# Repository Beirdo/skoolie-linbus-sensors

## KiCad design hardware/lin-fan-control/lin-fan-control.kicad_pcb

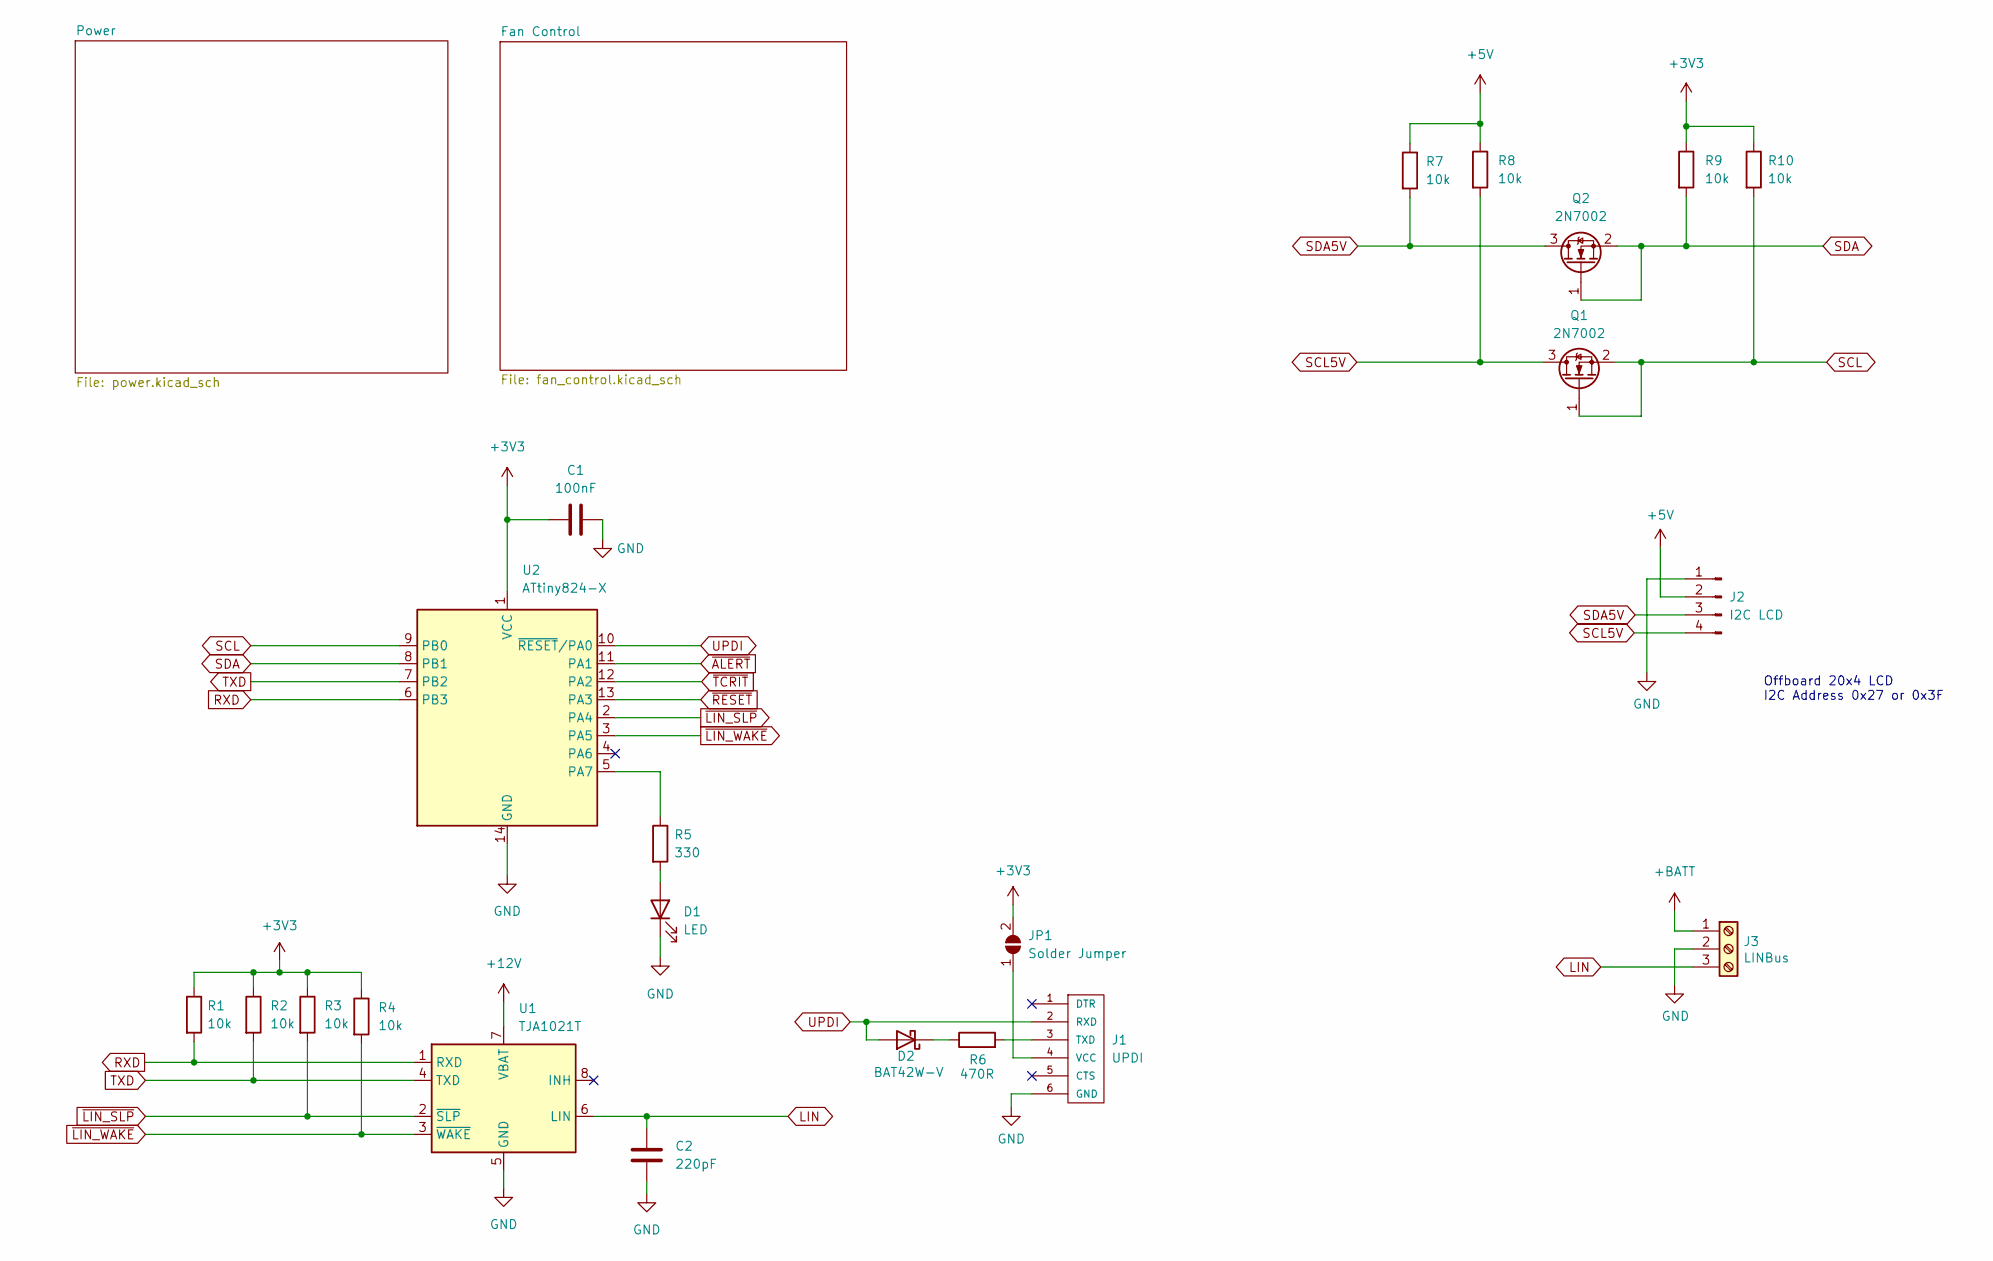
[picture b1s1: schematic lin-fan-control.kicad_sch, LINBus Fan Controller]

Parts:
C1: 100nF; C_0805_2012Metric_Pad1.18x1.45mm_HandSolder
C2: 220pF; C_0805_2012Metric_Pad1.18x1.45mm_HandSolder
D1: LED; LED_0805_2012Metric_Pad1.15x1.40mm_HandSolder
D2: BAT42W-V; D_SOD-123
J1: UPDI; FTDI-TARGET
J2: I2C LCD; PinHeader_1x04_P2.54mm_Vertical
J3: LINBus; TerminalBlock_TE_282834-3_1x03_P2.54mm_Horizontal
JP1: Solder Jumper; SolderJumper-2_P1.3mm_Open_TrianglePad1.0x1.5mm
Q1, Q2: 2N7002; SOT-23
R1, R2, R3, R4, R7, R8, R9, R10: 10k; R_0805_2012Metric_Pad1.20x1.40mm_HandSolder
R5: 330; R_0805_2012Metric_Pad1.20x1.40mm_HandSolder
R6: 470R; R_0805_2012Metric_Pad1.20x1.40mm_HandSolder
U1: TJA1021T; SOIC-8_3.9x4.9mm_P1.27mm
U2: ATtiny824-X; TSSOP-14_4.4x5mm_P0.65mm

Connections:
+3V3: C1.2, JP1.2 (B), R1.1, R2.1, R3.1, R4.1, R9.1, R10.1, U2.1 (VCC); also elsewhere on the board
+5V: J2.2, R7.1, R8.1; also elsewhere on the board
+12V: U1.7 (VBAT); also elsewhere on the board
+BATT: J3.1; also elsewhere on the board
GND: C1.1, C2.2, D1.1 (K), J1.6 (GND), J2.1, J3.2, U1.5 (GND), U2.14 (GND); also elsewhere on the board
LIN: C2.1, J3.3, U1.6 (LIN)
unnamed: D1.2 (A), R5.2
unnamed: D2.1 (K), R6.1
unnamed: J1.4 (VCC), JP1.1 (A)
unnamed: R5.1, U2.5 (PA7)
unnamed: J1.3 (TXD), R6.2
RXD: R1.2, U1.1 (RXD), U2.6 (PB3)
SCL: Q1.1 (G), Q1.2 (S), R10.2, U2.9 (PB0); also elsewhere on the board
SCL5V: J2.4, Q1.3 (D), R8.2
SDA: Q2.1 (G), Q2.2 (S), R9.2, U2.8 (PB1); also elsewhere on the board
SDA5V: J2.3, Q2.3 (D), R7.2
TXD: R2.2, U1.4 (TXD), U2.7 (PB2)
UPDI: D2.2 (A), J1.2 (RXD), U2.10 (~RESET/PA0)
~ALERT: U2.11 (PA1); also elsewhere on the board
~LIN_SLP: R3.2, U1.2 (~SLP), U2.2 (PA4)
~LIN_WAKE: R4.2, U1.3 (~WAKE), U2.3 (PA5)
~RESET: U2.13 (PA3)
~TCRIT: U2.12 (PA2); also elsewhere on the board

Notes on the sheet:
Offboard 20x4 LCD I2C Address 0x27 or 0x3F

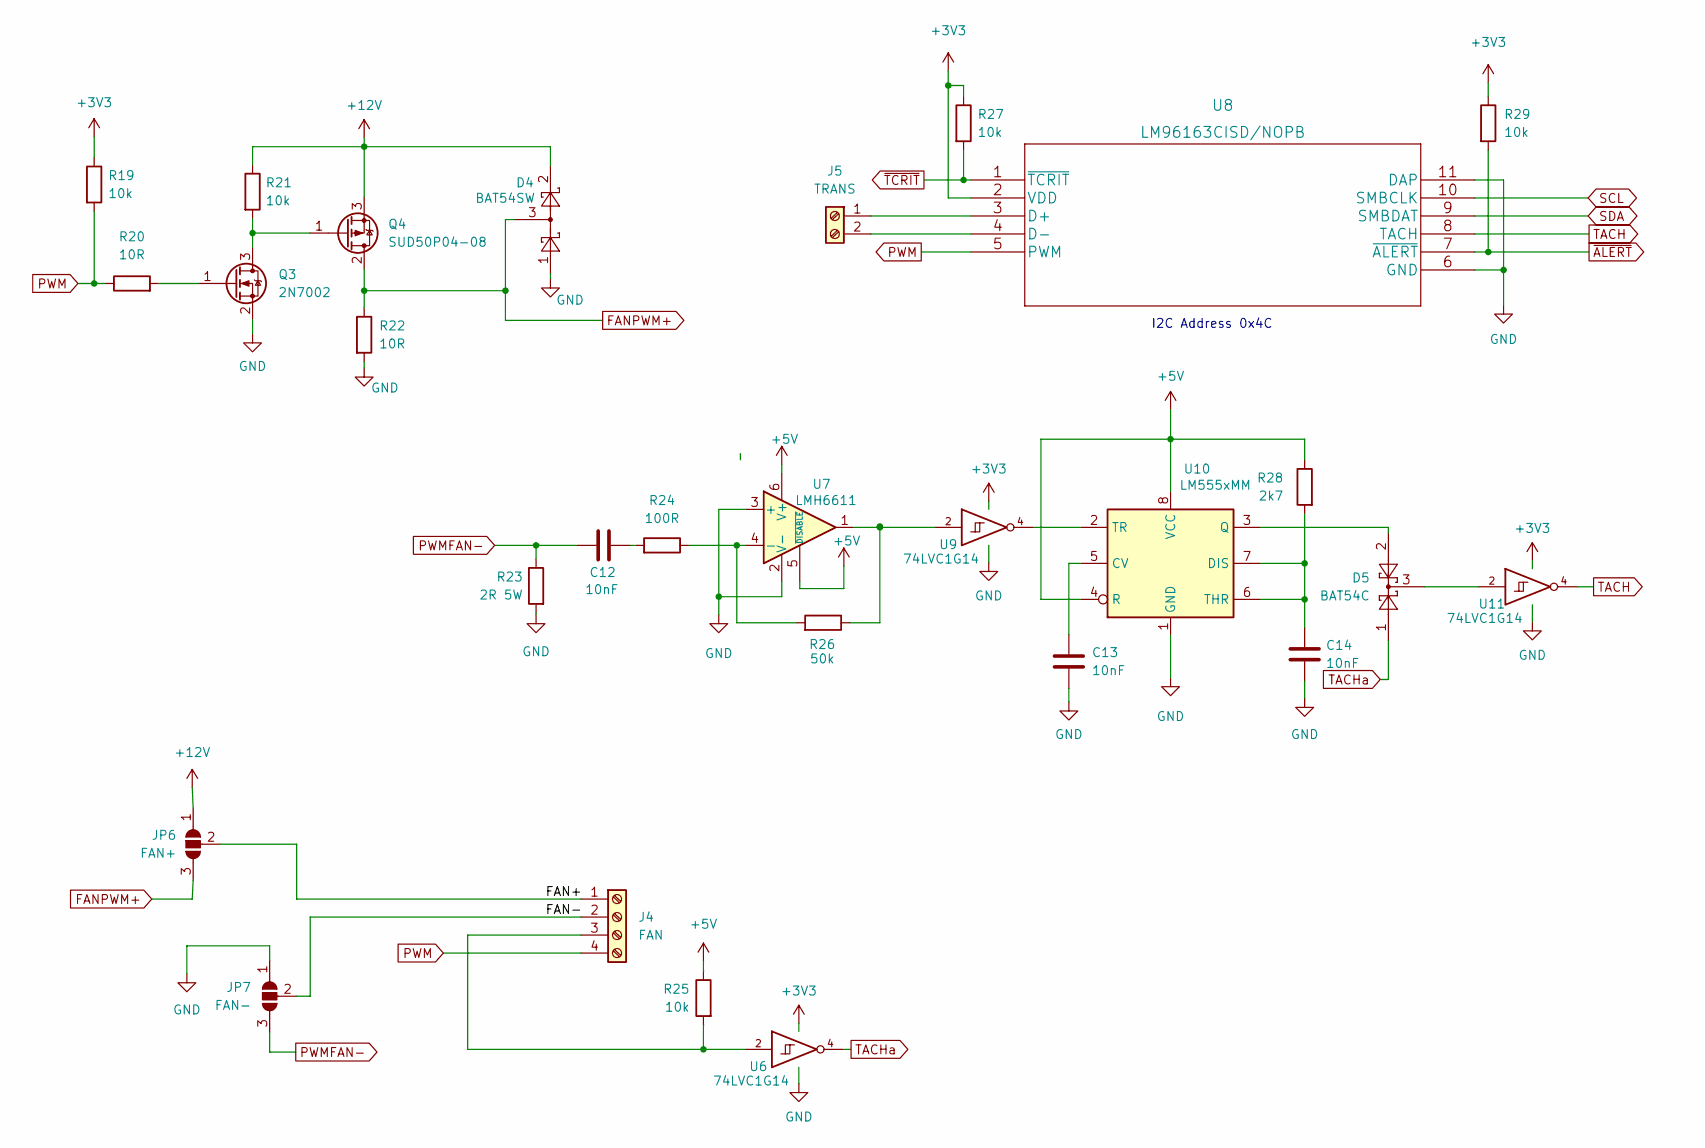
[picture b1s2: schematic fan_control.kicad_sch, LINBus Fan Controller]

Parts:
C12, C13, C14: 10nF; C_0805_2012Metric_Pad1.18x1.45mm_HandSolder
D4: BAT54SW; SOT-323_SC-70
D5: BAT54C; SOT-23
J4: FAN; TerminalBlock_TE_282834-4_1x04_P2.54mm_Horizontal
J5: TRANS; TerminalBlock_TE_282834-2_1x02_P2.54mm_Horizontal
JP6: FAN+; SolderJumper-3_P2.0mm_Open_TrianglePad1.0x1.5mm
JP7: FAN-; SolderJumper-3_P2.0mm_Open_TrianglePad1.0x1.5mm
Q3: 2N7002; SOT-23
Q4: SUD50P04-08; TO-252-2
R19, R21, R25, R27, R29: 10k; R_0805_2012Metric_Pad1.20x1.40mm_HandSolder
R20, R22: 10R; R_0805_2012Metric_Pad1.20x1.40mm_HandSolder
R23: 2R 5W; 355010RFT
R24: 100R; R_0805_2012Metric_Pad1.20x1.40mm_HandSolder
R26: 50k; R_0805_2012Metric_Pad1.20x1.40mm_HandSolder
R28: 2k7; R_0805_2012Metric_Pad1.20x1.40mm_HandSolder
U6, U9, U11: 74LVC1G14; SOT-353_SC-70-5_Handsoldering
U7: LMH6611; TSOT-23-6
U8: LM96163CISD/NOPB; LM96163CISD&slash_NOPB
U10: LM555xMM; VSSOP-8_3.0x3.0mm_P0.65mm

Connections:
+3V3: R19.1, R27.1, R29.1, U6.5 (VCC), U8.2 (VDD), U9.5 (VCC), U11.5 (VCC); also elsewhere on the board
+5V: R25.1, R28.1, U7.5 (~DISABLE), U7.6 (V+), U10.4 (R), U10.8 (VCC); also elsewhere on the board
+12V: D4.2, JP6.1 (A), Q4.3 (S), R21.1; also elsewhere on the board
/Fan Control/FAN+: J4.1, JP6.2 (C)
/Fan Control/FAN-: J4.2, JP7.2 (C)
FANPWM+: D4.3, JP6.3 (B), Q4.2 (D), R22.1
GND: C13.2, C14.2, D4.1, JP7.1 (A), Q3.2 (S), R22.2, R23.2, U6.3 (GND), U7.2 (V-), U7.3 (+), U8.6 (GND), U8.11 (DAP), U9.3 (GND), U10.1 (GND), U11.3 (GND); also elsewhere on the board
unnamed: C12.1, R24.2
unnamed: C13.1, U10.5 (CV)
unnamed: C14.1, R28.2, U10.6 (THR), U10.7 (DIS)
unnamed: D5.2, U10.3 (Q)
unnamed: D5.3, U11.2
unnamed: J4.3, R25.2, U6.2
unnamed: J5.1, U8.3 (D+)
unnamed: J5.2, U8.4 (D-)
unnamed: Q3.1 (G), R20.2
unnamed: Q3.3 (D), Q4.1 (G), R21.2
unnamed: R24.1, R26.2, U7.4 (-)
unnamed: R26.1, U7.1, U9.2
unnamed: U9.4, U10.2 (TR)
PWM: J4.4, R19.2, R20.1, U8.5 (PWM)
PWMFAN-: C12.2, JP7.3 (B), R23.1
SCL: U8.10 (SMBCLK); also elsewhere on the board
SDA: U8.9 (SMBDAT); also elsewhere on the board
TACH: U8.8 (TACH), U11.4
TACHa: D5.1, U6.4
~ALERT: R29.2, U8.7 (~ALERT); also elsewhere on the board
~TCRIT: R27.2, U8.1 (~TCRIT); also elsewhere on the board

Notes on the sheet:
I2C Address 0x4C

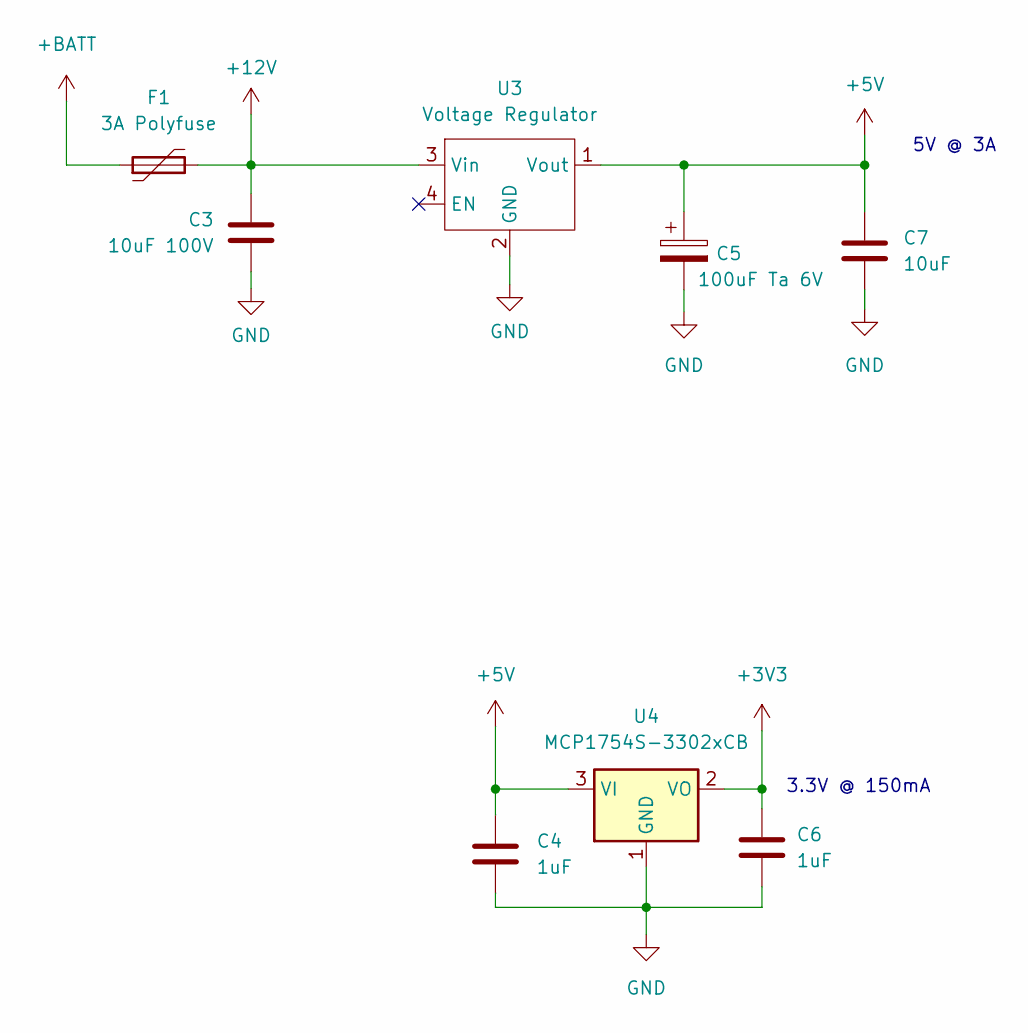
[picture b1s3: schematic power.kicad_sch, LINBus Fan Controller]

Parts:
C3: 10uF 100V; C_1210_3225Metric_Pad1.33x2.70mm_HandSolder
C4, C6: 1uF; C_0805_2012Metric_Pad1.18x1.45mm_HandSolder
C5: 100uF Ta 6V; CP_EIA-3216-10_Kemet-I_Pad1.58x1.35mm_HandSolder
C7: 10uF; C_0805_2012Metric_Pad1.18x1.45mm_HandSolder
F1: 3A Polyfuse; R_1812_4532Metric_Pad1.30x3.40mm_HandSolder; Digikey F2772CT-ND
U3: Voltage Regulator; Switching_Regulator_Module
U4: MCP1754S-3302xCB; SOT-23

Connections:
+3V3: C6.1, U4.2 (VO); also elsewhere on the board
+5V: C4.1, C5.1, C7.1, U3.1 (Vout), U4.3 (VI); also elsewhere on the board
+12V: C3.1, F1.2, U3.3 (Vin); also elsewhere on the board
+BATT: F1.1; also elsewhere on the board
GND: C3.2, C4.2, C5.2, C6.2, C7.2, U3.2 (GND), U4.1 (GND); also elsewhere on the board

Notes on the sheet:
5V @ 3A
3.3V @ 150mA

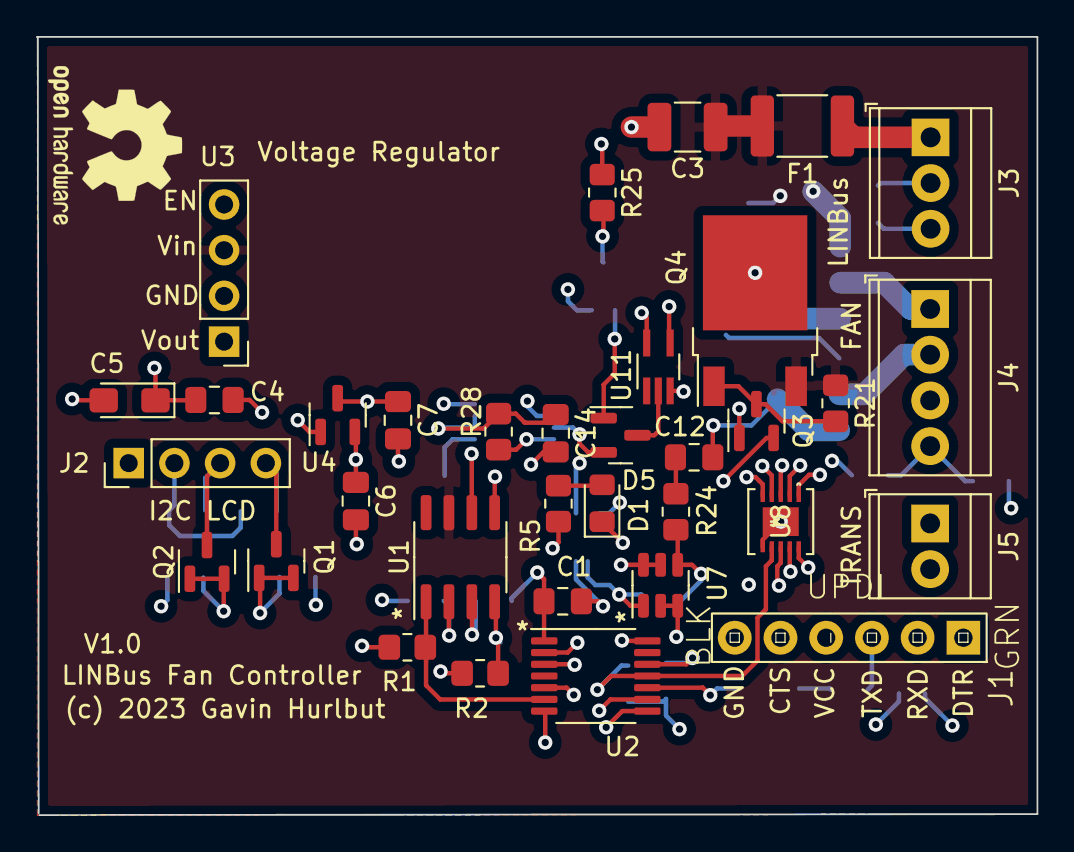
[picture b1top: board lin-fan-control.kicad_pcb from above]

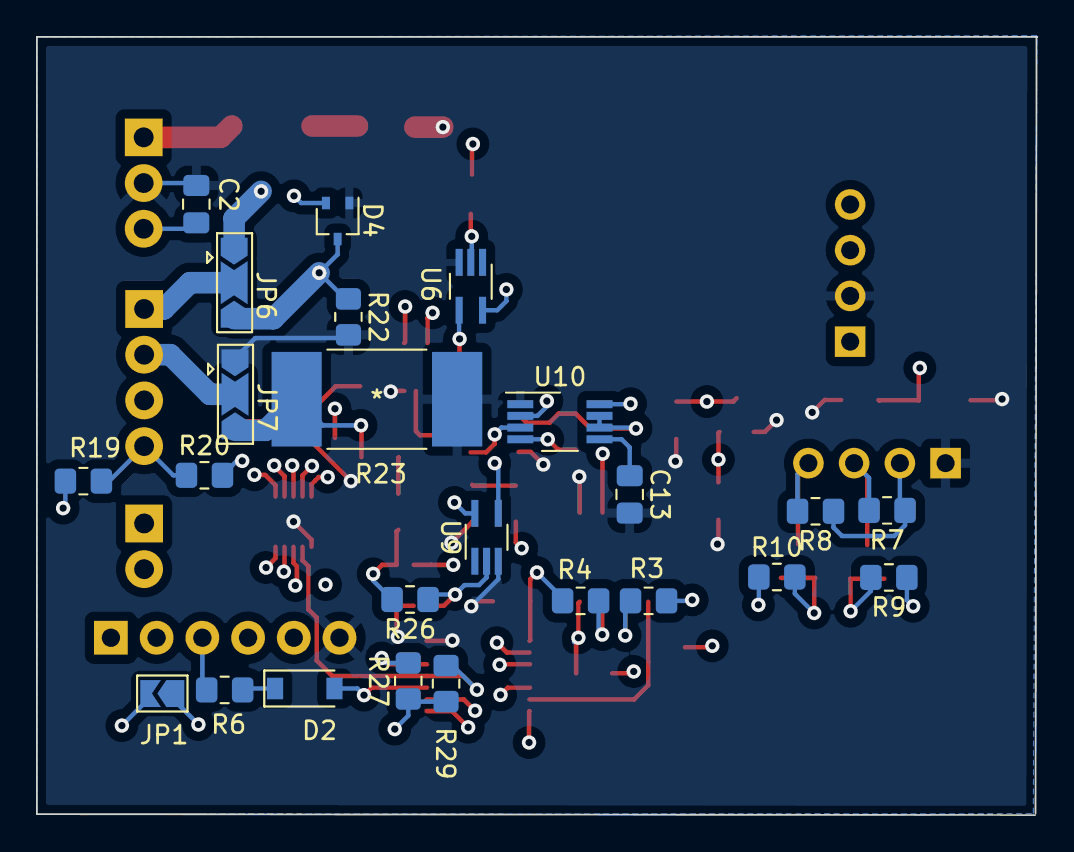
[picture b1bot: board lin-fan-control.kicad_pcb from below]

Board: 4 copper layers, 55.6 x 43.2 mm, 58 parts (24 on the bottom side), 42 nets.

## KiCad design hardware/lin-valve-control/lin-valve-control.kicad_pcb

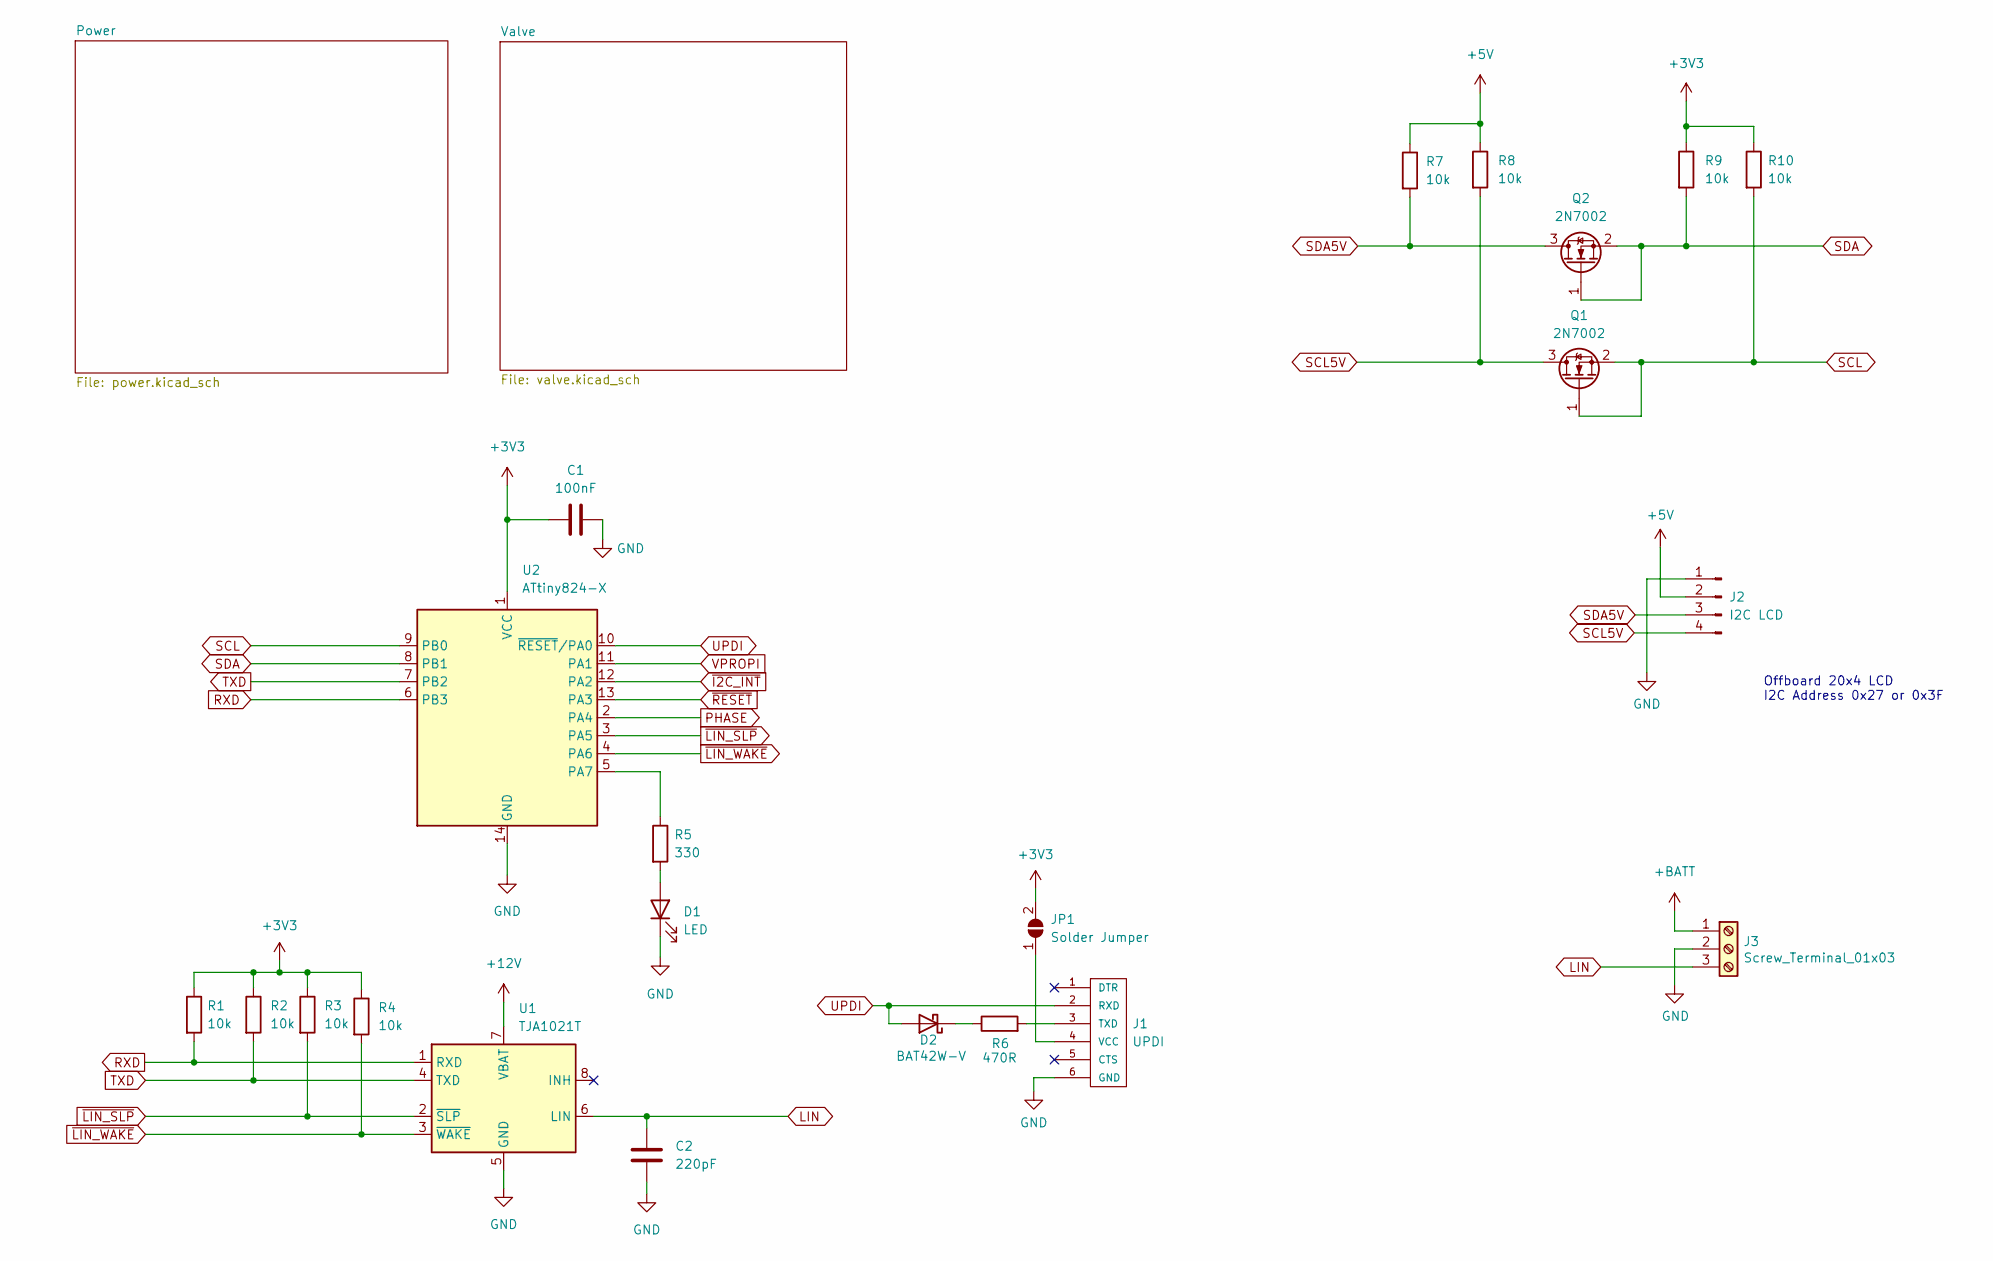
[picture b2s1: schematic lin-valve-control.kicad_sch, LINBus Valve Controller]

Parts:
C1: 100nF; C_0805_2012Metric_Pad1.18x1.45mm_HandSolder
C2: 220pF; C_0805_2012Metric_Pad1.18x1.45mm_HandSolder
D1: LED; LED_0805_2012Metric_Pad1.15x1.40mm_HandSolder
D2: BAT42W-V; D_SOD-123
J1: UPDI; FTDI-TARGET
J2: I2C LCD; PinHeader_1x04_P2.54mm_Vertical
J3: Screw_Terminal_01x03; TerminalBlock_TE_282834-3_1x03_P2.54mm_Horizontal
JP1: Solder Jumper; SolderJumper-2_P1.3mm_Open_TrianglePad1.0x1.5mm
Q1, Q2: 2N7002; SOT-23
R1, R2, R3, R4, R7, R8, R9, R10: 10k; R_0805_2012Metric_Pad1.20x1.40mm_HandSolder
R5: 330; R_0805_2012Metric_Pad1.20x1.40mm_HandSolder
R6: 470R; R_0805_2012Metric_Pad1.20x1.40mm_HandSolder
U1: TJA1021T; SOIC-8_3.9x4.9mm_P1.27mm
U2: ATtiny824-X; TSSOP-14_4.4x5mm_P0.65mm

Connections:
+3V3: C1.2, JP1.2 (B), R1.1, R2.1, R3.1, R4.1, R9.1, R10.1, U2.1 (VCC); also elsewhere on the board
+5V: J2.2, R7.1, R8.1; also elsewhere on the board
+12V: U1.7 (VBAT); also elsewhere on the board
+BATT: J3.1; also elsewhere on the board
GND: C1.1, C2.2, D1.1 (K), J1.6 (GND), J2.1, J3.2, U1.5 (GND), U2.14 (GND); also elsewhere on the board
LIN: C2.1, J3.3, U1.6 (LIN)
unnamed: D1.2 (A), R5.2
unnamed: D2.1 (K), R6.1
unnamed: J1.3 (TXD), R6.2
unnamed: J1.4 (VCC), JP1.1 (A)
unnamed: R5.1, U2.5 (PA7)
PHASE: U2.2 (PA4); also elsewhere on the board
RXD: R1.2, U1.1 (RXD), U2.6 (PB3)
SCL: Q1.1 (G), Q1.2 (S), R10.2, U2.9 (PB0); also elsewhere on the board
SCL5V: J2.4, Q1.3 (D), R8.2
SDA: Q2.1 (G), Q2.2 (S), R9.2, U2.8 (PB1); also elsewhere on the board
SDA5V: J2.3, Q2.3 (D), R7.2
TXD: R2.2, U1.4 (TXD), U2.7 (PB2)
UPDI: D2.2 (A), J1.2 (RXD), U2.10 (~RESET/PA0)
VPROPI: U2.11 (PA1); also elsewhere on the board
~I2C_INT: U2.12 (PA2); also elsewhere on the board
~LIN_SLP: R3.2, U1.2 (~SLP), U2.3 (PA5)
~LIN_WAKE: R4.2, U1.3 (~WAKE), U2.4 (PA6)
~RESET: U2.13 (PA3)

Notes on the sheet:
Offboard 20x4 LCD I2C Address 0x27 or 0x3F

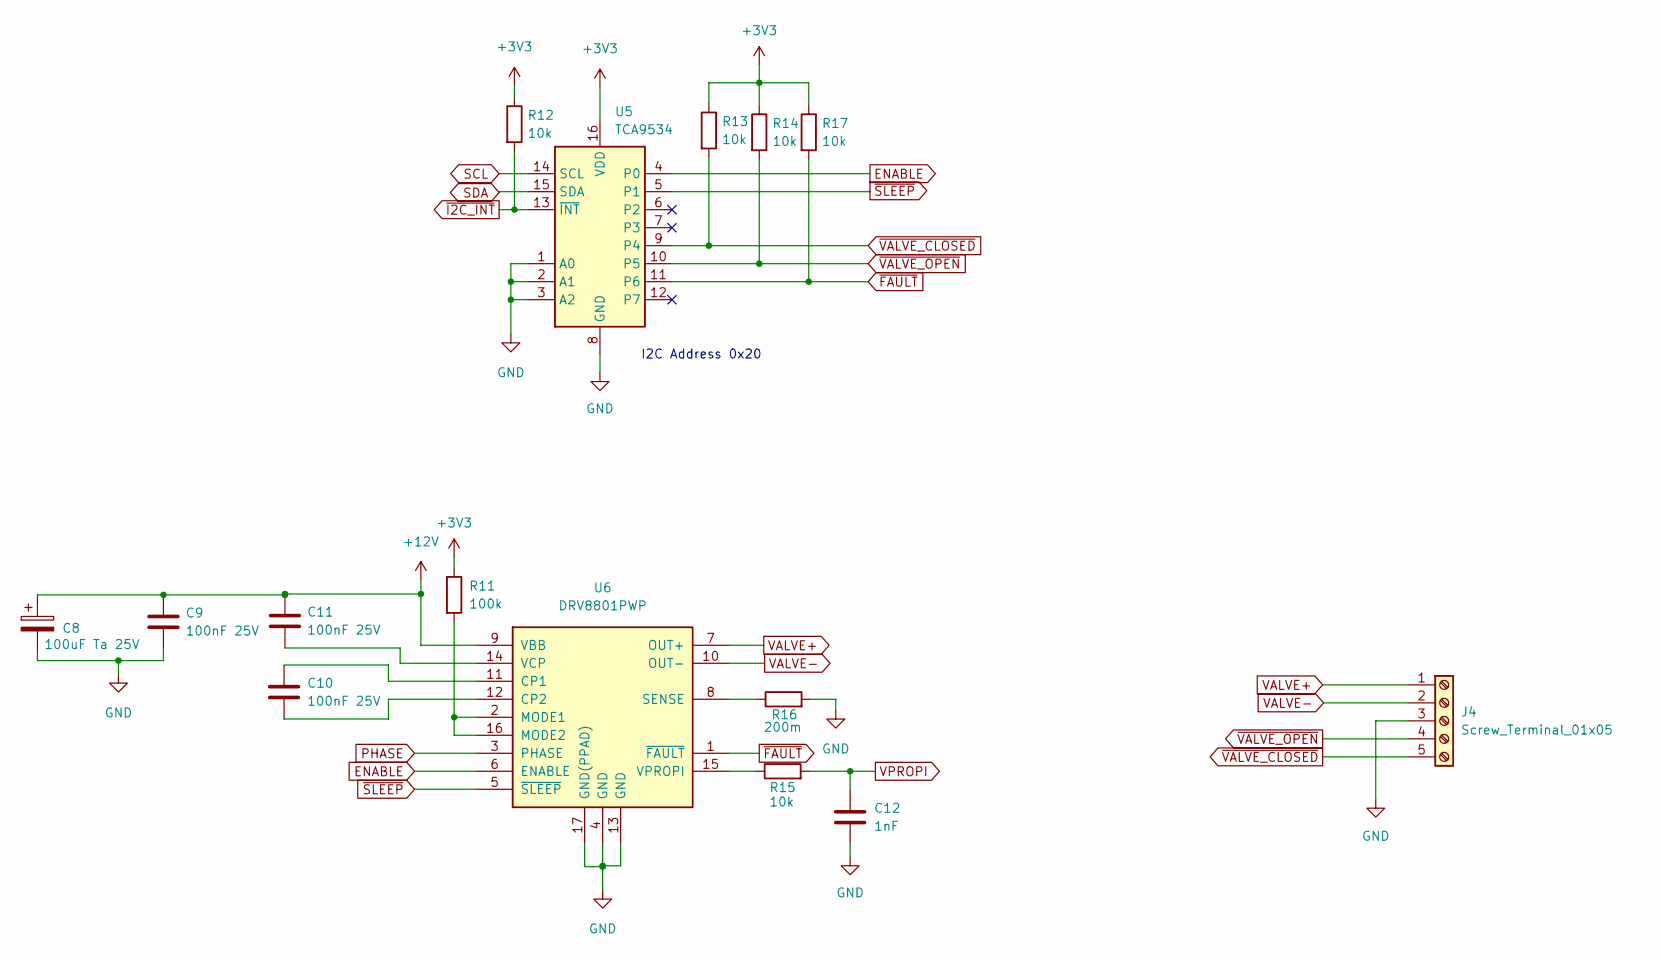
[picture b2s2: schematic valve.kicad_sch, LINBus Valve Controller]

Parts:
C8: 100uF Ta 25V; CP_EIA-7343-20_Kemet-V_Pad2.25x2.55mm_HandSolder
C9, C10, C11: 100nF 25V; C_1206_3216Metric_Pad1.33x1.80mm_HandSolder
C12: 1nF; C_0805_2012Metric_Pad1.18x1.45mm_HandSolder
J4: Screw_Terminal_01x05; TerminalBlock_TE_282834-5_1x05_P2.54mm_Horizontal
R11: 100k; R_0805_2012Metric_Pad1.20x1.40mm_HandSolder
R12, R13, R14, R15, R17: 10k; R_0805_2012Metric_Pad1.20x1.40mm_HandSolder
R16: 200m; R_0805_2012Metric_Pad1.20x1.40mm_HandSolder
U5: TCA9534; TSSOP-16_4.4x5mm_P0.65mm
U6: DRV8801PWP; HTSSOP-16-1EP_4.4x5mm_P0.65mm_EP3.4x5mm_Mask3x3mm_ThermalVi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

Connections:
+3V3: R11.1, R12.1, R13.1, R14.1, R17.1, U5.16 (VDD); also elsewhere on the board
+12V: C8.1, C9.1, C11.1, U6.9 (VBB); also elsewhere on the board
ENABLE: U5.4 (P0), U6.6 (ENABLE)
GND: C8.2, C9.2, C12.2, J4.3, R16.2, U5.1 (A0), U5.2 (A1), U5.3 (A2), U5.8 (GND), U6.4 (GND), U6.13 (GND), U6.17 (GND(PPAD)); also elsewhere on the board
unnamed: C10.1, U6.11 (CP1)
unnamed: C10.2, U6.12 (CP2)
unnamed: C11.2, U6.14 (VCP)
unnamed: R11.2, U6.2 (MODE1), U6.16 (MODE2)
unnamed: R15.1, U6.15 (VPROPI)
unnamed: R16.1, U6.8 (SENSE)
PHASE: U6.3 (PHASE); also elsewhere on the board
SCL: U5.14 (SCL); also elsewhere on the board
SDA: U5.15 (SDA); also elsewhere on the board
VALVE+: J4.1, U6.7 (OUT+)
VALVE-: J4.2, U6.10 (OUT-)
VPROPI: C12.1, R15.2; also elsewhere on the board
~FAULT: R17.2, U5.11 (P6), U6.1 (~FAULT)
~I2C_INT: R12.2, U5.13 (~INT); also elsewhere on the board
~SLEEP: U5.5 (P1), U6.5 (~SLEEP)
~VALVE_CLOSED: J4.5, R13.2, U5.9 (P4)
~VALVE_OPEN: J4.4, R14.2, U5.10 (P5)

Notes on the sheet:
I2C Address 0x20

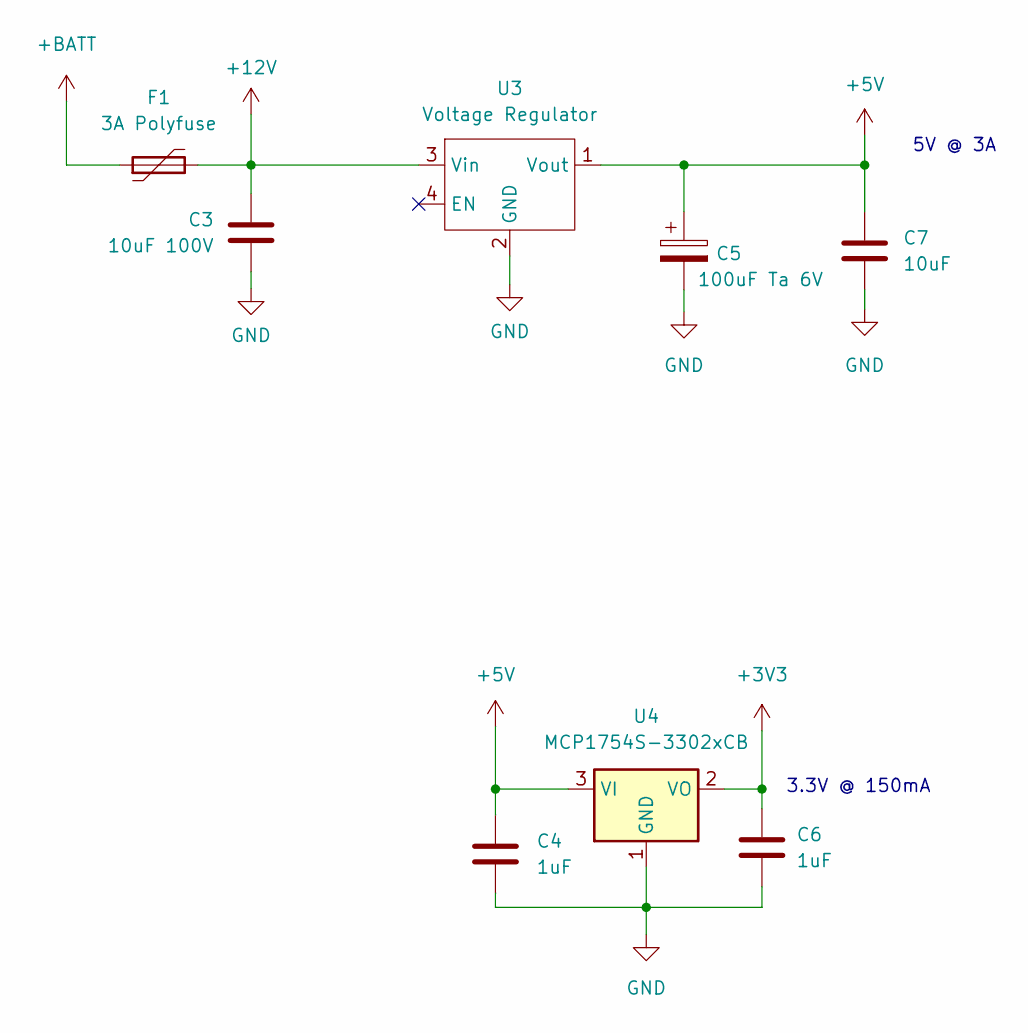
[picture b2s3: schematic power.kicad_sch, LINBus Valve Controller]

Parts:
C3: 10uF 100V; C_1210_3225Metric_Pad1.33x2.70mm_HandSolder
C4, C6: 1uF; C_0805_2012Metric_Pad1.18x1.45mm_HandSolder
C5: 100uF Ta 6V; CP_EIA-3216-10_Kemet-I_Pad1.58x1.35mm_HandSolder
C7: 10uF; C_0805_2012Metric_Pad1.18x1.45mm_HandSolder
F1: 3A Polyfuse; R_1812_4532Metric_Pad1.30x3.40mm_HandSolder; Digikey F2772CT-ND
U3: Voltage Regulator; Switching_Regulator_Module
U4: MCP1754S-3302xCB; SOT-23

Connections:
+3V3: C6.1, U4.2 (VO); also elsewhere on the board
+5V: C4.1, C5.1, C7.1, U3.1 (Vout), U4.3 (VI); also elsewhere on the board
+12V: C3.1, F1.2, U3.3 (Vin); also elsewhere on the board
+BATT: F1.1; also elsewhere on the board
GND: C3.2, C4.2, C5.2, C6.2, C7.2, U3.2 (GND), U4.1 (GND); also elsewhere on the board

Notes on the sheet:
3.3V @ 150mA
5V @ 3A

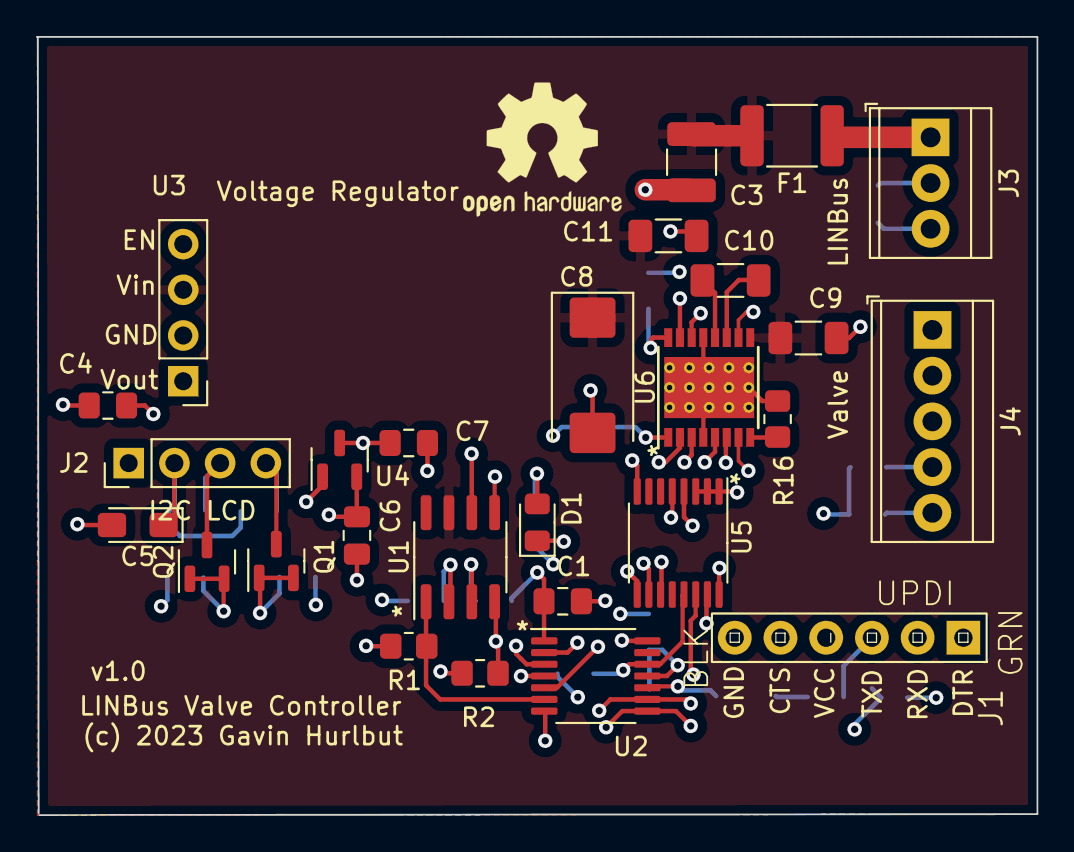
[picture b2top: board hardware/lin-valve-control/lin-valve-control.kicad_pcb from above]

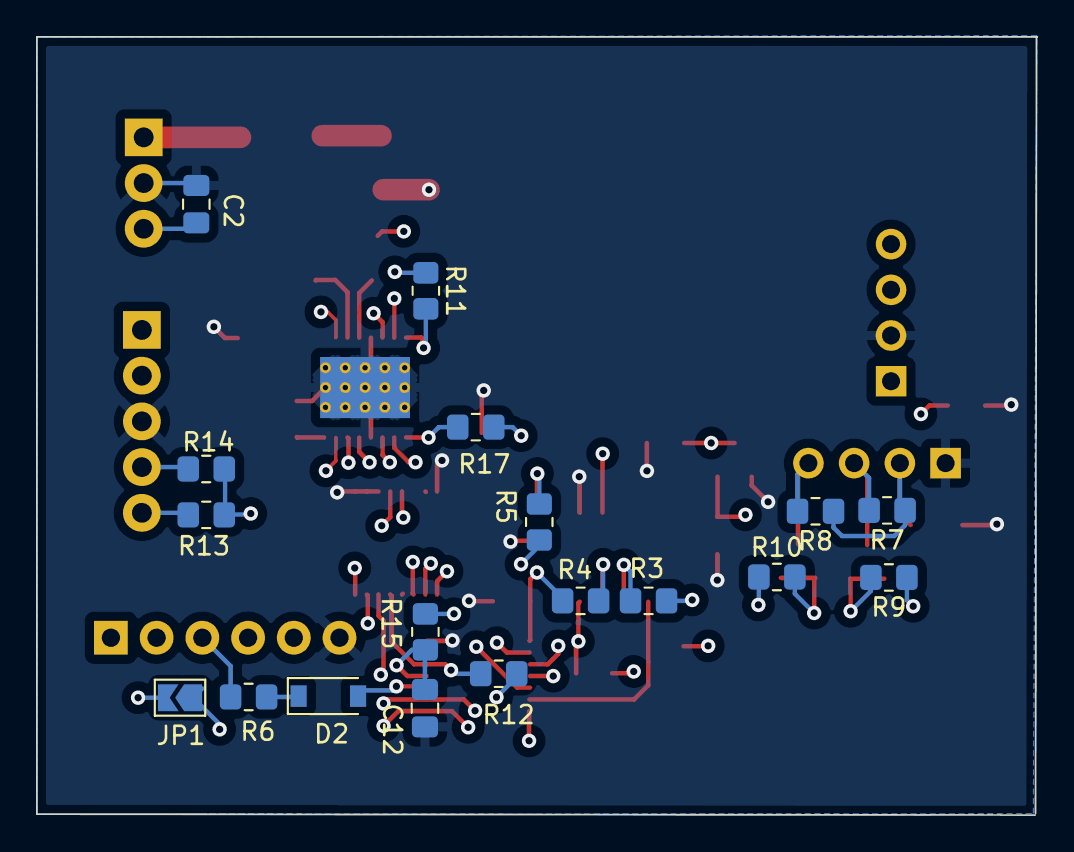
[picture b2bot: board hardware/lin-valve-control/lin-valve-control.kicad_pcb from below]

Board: 4 copper layers, 55.6 x 43.2 mm, 45 parts (18 on the bottom side), 36 nets.

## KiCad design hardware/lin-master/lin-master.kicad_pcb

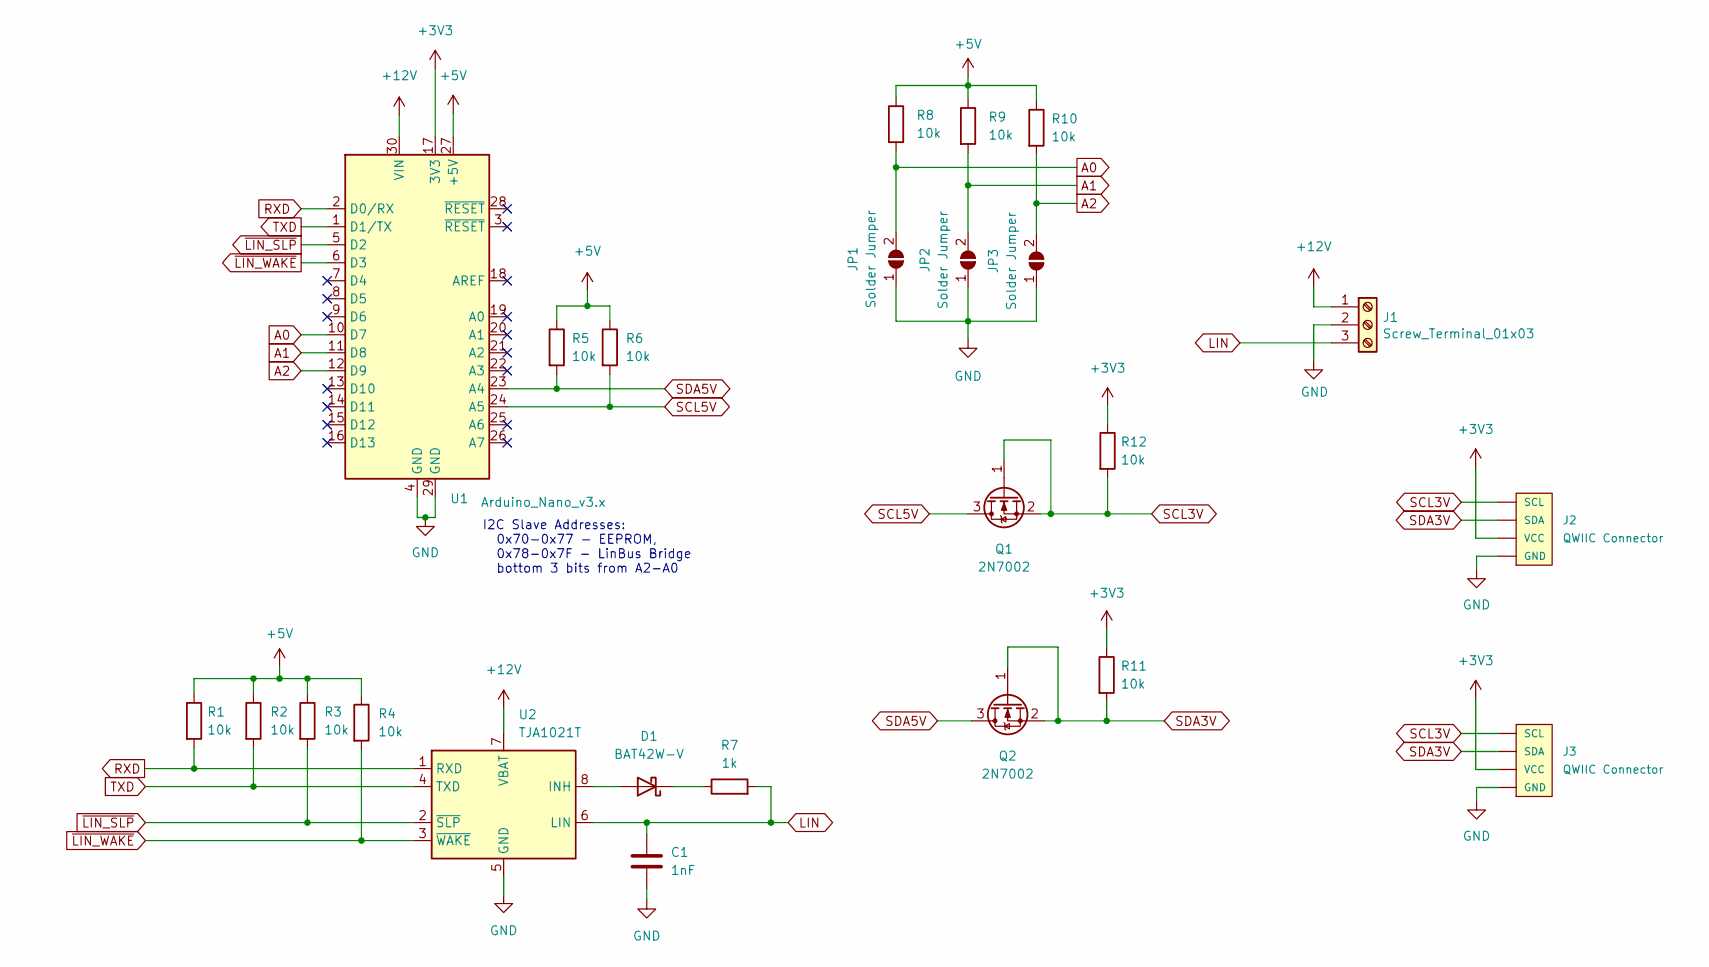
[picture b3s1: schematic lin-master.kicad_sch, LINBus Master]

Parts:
C1: 1nF; C_0805_2012Metric_Pad1.18x1.45mm_HandSolder
D1: BAT42W-V; D_SOD-123
J1: Screw_Terminal_01x03; TerminalBlock_TE_282834-3_1x03_P2.54mm_Horizontal
J2, J3: QWIIC Connector; 1X04_1MM_RA
JP1, JP2, JP3: Solder Jumper; SolderJumper-2_P1.3mm_Open_TrianglePad1.0x1.5mm
Q1, Q2: 2N7002; SOT-23
R1, R2, R3, R4, R5, R6, R8, R9, R10, R11, R12: 10k; R_0805_2012Metric_Pad1.20x1.40mm_HandSolder
R7: 1k; R_0805_2012Metric_Pad1.20x1.40mm_HandSolder
U1: Arduino_Nano_v3.x; Arduino_Nano
U2: TJA1021T; SOIC-8_3.9x4.9mm_P1.27mm

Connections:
+3V3: J2.2 (VCC), J3.2 (VCC), R11.1, R12.1, U1.17 (3V3)
+5V: R1.1, R2.1, R3.1, R4.1, R5.1, R6.1, R8.1, R9.1, R10.1, U1.27 (+5V)
+12V: J1.1, U1.30 (VIN), U2.7 (VBAT)
A0: JP1.2 (B), R8.2, U1.10 (D7)
A1: JP2.2 (B), R9.2, U1.11 (D8)
A2: JP3.2 (B), R10.2, U1.12 (D9)
GND: C1.2, J1.2, J2.1 (GND), J3.1 (GND), JP1.1 (A), JP2.1 (A), JP3.1 (A), U1.4 (GND), U1.29 (GND), U2.5 (GND)
LIN: C1.1, J1.3, R7.2, U2.6 (LIN)
unnamed: D1.1 (K), R7.1
unnamed: D1.2 (A), U2.8 (INH)
RXD: R1.2, U1.2 (D0/RX), U2.1 (RXD)
SCL3V: J2.4 (SCL), J3.4 (SCL), Q1.1 (G), Q1.2 (S), R12.2
SCL5V: Q1.3 (D), R6.2, U1.24 (A5)
SDA3V: J2.3 (SDA), J3.3 (SDA), Q2.1 (G), Q2.2 (S), R11.2
SDA5V: Q2.3 (D), R5.2, U1.23 (A4)
TXD: R2.2, U1.1 (D1/TX), U2.4 (TXD)
~LIN_SLP: R3.2, U1.5 (D2), U2.2 (~SLP)
~LIN_WAKE: R4.2, U1.6 (D3), U2.3 (~WAKE)

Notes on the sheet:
I2C Slave Addresses: 0x70-0x77 - EEPROM, 0x78-0x7F - LinBus Bridge bottom 3 bits from A2-A0

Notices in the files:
hardware/lin-fan-control/lin-fan-control.kicad_pcb:
(c) 2023 Gavin Hurlbut
parts and their libraries:
Copyright 2021 Accelerated Designs. All rights reserved.
